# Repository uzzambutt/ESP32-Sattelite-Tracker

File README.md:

<div align="center">

# ESP32 Satellite Tracker — Orbital Ops v10.0

**Designer:** [Muhammad Uzzam Butt](https://github.com/uzzambutt) // Made for Offtrack YSWS

*PCB screenshot, Uses SGP4 to calculate orbital sattelite mechanics natively.*

</div>

An ESP32-based automated satellite tracking system that drives a two-axis antenna mount using stepper motors, propagates satellite positions in real time with the SGP4 algorithm, and serves a live web dashboard over WiFi. The system supports a satellite queue, 24-hour pass scheduling, Doppler shift calculation, IMU-assisted elevation correction, weather data, satellite footprint visualization, and full EasyComm II compatibility for use with applications such as Look4Sat.

---

## Table of Contents

1. [Features](#features)
2. [Hardware Requirements](#hardware-requirements)
3. [Wiring Reference](#wiring-reference)
4. [Software Dependencies](#software-dependencies)
5. [File Structure](#file-structure)
6. [Configuration](#configuration)
7. [secrets.h Setup](#secretsh-setup)
8. [Building and Flashing](#building-and-flashing)
9. [First Boot](#first-boot)
10. [Web Dashboard](#web-dashboard)
11. [TFT Screen Reference](#tft-screen-reference)
12. [REST API Reference](#rest-api-reference)
13. [EasyComm II Interface](#easycomm-ii-interface)
14. [Satellite Queue](#satellite-queue)
15. [Pass Schedule](#pass-schedule)
16. [Weather Integration](#weather-integration)
17. [Auto-Park](#auto-park)
18. [OTA Updates](#ota-updates)
19. [Troubleshooting](#troubleshooting)

---

## Features

**Tracking and Propagation**
- Real-time SGP4/SDP4 satellite position propagation via the Sgp4 Arduino library
- Two-axis antenna control (azimuth and elevation) using AccelStepper with smooth acceleration
- Satellite queue: track up to 8 satellites sequentially, with automatic advancement after each pass
- 24-hour pass schedule computed for all queued satellites simultaneously, sorted by AOS time
- Real-time Doppler frequency shift calculation for multi-band (145.8, 435.8, 1268.0 MHz)
- Accurate satellite footprint computation using true orbital altitude and Earth-radius geometry
- Atmospheric drag refraction correction (Bennett 1982) for low-elevation passes

**Displays**
- 240x320 ST7789 TFT with 6 cycling screens:
  - Main HUD: target/current Az/El, pass countdown, Doppler, range, signal bars, radar
  - Pass Schedule: next 24 h passes for all queued satellites
  - IMU Drift Graph: real-time Kalman error history plot
  - Satellite Footprint: geometrically accurate overhead map with nadir, coverage area, arc angle
  - Orbital Elements: Inclination, RAAN, Eccentricity, Period, Perigee/Apogee, Orbit Type, TLE Age
  - Weather: temperature, feels-like, wind speed/direction, humidity, pressure, NOAA Kp Index
- Animated radar with satellite trajectory, AOS/LOS markers, and physics-based footprint ring
- Linux-style boot log with colour-coded status tags on TFT

**Networking and Control**
- WiFi station mode with AP fallback portal for credential setup
- Web dashboard served from PROGMEM over port 80 (ESPAsyncWebServer)
- WebSocket push telemetry at 1 Hz
- EasyComm II protocol over TCP port 4533 for Look4Sat and compatible clients
- mDNS hostname: sattracker.local
- ArduinoOTA firmware updates over WiFi

**Sensors and Intelligence**
- MPU6050 IMU with two-axis Kalman filter
- Accelerometer spike rejection, gyro deadband, and software low-pass filter
- **Note:** The MPU6050 is a 6-axis IMU (Gyro+Accel) and only measures gravity vectors. It can correct wind-drift or step-skipping on the **Elevation** axis, but it cannot determine absolute Azimuth heading without a magnetometer.
- NTP time synchronisation via pool.ntp.org
- Real-time NOAA Space Weather (Geomagnetic Kp index) parsing

**Persistence**
- TLE stored to LittleFS (/tle.txt) and re-loaded on boot
- Observer grid square, operating mode, weather city, and WiFi credentials stored in NVS (Preferences)

---

## Hardware Requirements

| Component | Notes |
|-----------|-------|
| ESP32 development board | 30-pin or 38-pin, dual-core. Tested on ESP32-WROOM-32 |
| ST7789 TFT display | 240x320, SPI interface, 3.3 V logic |
| MPU6050 / GY-521 | I2C IMU, address 0x68 |
| Azimuth stepper driver | Step/Dir interface (e.g. DRV8825, A4988, TB6600) |
| Elevation stepper driver | Step/Dir interface |
| Azimuth stepper motor | NEMA 17 or NEMA 23 depending on load |
| Elevation stepper motor | NEMA 17 or NEMA 23 depending on load |
| Power supply | 12 V or 24 V for stepper drivers; 3.3 V/5 V for ESP32 |

---

## Wiring Reference

### TFT Display (ST7789, SPI)

| TFT Pin | ESP32 Pin | Config Constant |
|---------|-----------|-----------------|
| CS | GPIO 15 | TFT_CS |
| DC | GPIO 2 | TFT_DC |
| RST | GPIO 4 | TFT_RST |
| SCK | GPIO 18 | Hardware SPI (VSPI) |
| MOSI | GPIO 23 | Hardware SPI (VSPI) |
| VCC | 3.3 V | |
| GND | GND | |

### MPU6050 IMU (I2C)

| MPU6050 Pin | ESP32 Pin | Config Constant |
|-------------|-----------|-----------------|
| VCC | 3.3 V | |
| GND | GND | |
| SDA | GPIO 21 | MPU_SDA |
| SCL | GPIO 22 | MPU_SCL |
| AD0 | GND | Sets I2C address to 0x68 |

### Azimuth Stepper Driver

| Signal | ESP32 Pin | Config Constant |
|--------|-----------|-----------------|
| STEP | GPIO 32 | AZ_STEP |
| DIR | GPIO 14 | AZ_DIR |
| ENABLE | GPIO 25 | ENABLE_PIN (shared with elevation) |

### Elevation Stepper Driver

| Signal | ESP32 Pin | Config Constant |
|--------|-----------|-----------------|
| STEP | GPIO 27 | EL_STEP |
| DIR | GPIO 26 | EL_DIR |
| ENABLE | GPIO 25 | ENABLE_PIN (shared with azimuth) |

### Button

| Function | ESP32 Pin | Notes |
|----------|-----------|-------|
| Screen cycle | GPIO 0 | IO0 / BOOT button. Active LOW, internal pull-up enabled |

---

## Software Dependencies

Install all of the following through the Arduino IDE Library Manager or manually:

| Library | Purpose |
|---------|---------|
| Sgp4 | SGP4/SDP4 orbital propagation |
| Adafruit_GFX | TFT graphics primitives |
| Adafruit_ST7789 | ST7789 TFT driver |
| AccelStepper | Stepper motor control with acceleration profiles |
| ESPAsyncWebServer | Asynchronous HTTP and WebSocket server |
| AsyncTCP | Required by ESPAsyncWebServer |
| ArduinoJson | JSON serialisation and deserialisation |
| NTPClient | NTP time synchronisation |
| ArduinoOTA | Over-the-air firmware updates |
| ESPmDNS | mDNS hostname resolution |
| LittleFS (built-in) | Filesystem for TLE storage |
| Preferences (built-in) | NVS key-value persistent storage |
| HTTPClient (built-in) | OpenWeatherMap API requests |
| Wire (built-in) | I2C communication for MPU6050 |

Board package: Install "ESP32 by Espressif Systems" via Boards Manager.
Tested with Arduino IDE 2.x and ESP32 core 2.0.x or 3.x.

---

## File Structure

```
ESP32_Sat_Tracker/
├── ESP32_Sat_Tracker.ino   Main sketch: globals, setup(), loop(), Core0 task,
│                            web server handlers, SGP4 runner, pass prediction,
│                            queue logic, Doppler, footprint, weather fetch
├── Config.h                 Pin definitions, colour palette, tuning parameters
├── secrets.h                WiFi credentials and OWM API key (excluded from VCS)
├── Display_Module.h         All TFT drawing functions (5 screens + radar engine)
├── Runtime_Module.h         EasyComm II parser and SGP4 runtime update function
├── Web_Pages.h              PROGMEM HTML/CSS/JS dashboard and WiFi setup portal
├── qrcodegen.h              QR code generator (used on boot screen)
└── data/                    LittleFS data directory
```

---

## Configuration

All hardware pins, timing constants, and tuning parameters are defined in Config.h. No other file needs editing for a pin reassignment.

### Key Constants

| Constant | Default | Description |
|----------|---------|-------------|
| BTN_PIN | 0 | GPIO for screen-cycle button |
| SCREEN_COUNT | 5 | Number of TFT screens |
| MAX_QUEUED_SATS | 8 | Maximum satellites in the tracking queue |
| MAX_SCHEDULED_PASSES | 48 | Maximum passes in the 24-hour schedule |
| PARK_IDLE_SEC | 300 | Seconds of inactivity before auto-park |
| PARK_AZ | 0.0 | Park azimuth in degrees |
| PARK_EL | 0.0 | Park elevation in degrees |
| WEATHER_INTERVAL_MS | 600000 | Weather fetch interval in milliseconds (10 min) |
| IMU_CORRECT_ENABLED | false | Enable IMU-assisted elevation correction |
| IMU_CORRECT_THRESH | 2.5 | Error threshold in degrees to trigger IMU correction |

### Steps Per Degree

The stepper resolution is set in the main sketch:

```cpp
const float STEPS_PER_DEG = 8.88f;
```

Calculate your value as:

    STEPS_PER_DEG = (motor_full_steps * driver_microsteps * gear_ratio) / 360

Example: 200 steps/rev * 16 microsteps * 1:1 gearbox / 360 = 8.89 steps/degree.

---

## secrets.h Setup

Create this file in the sketch directory. It is excluded from version control.

```cpp
// secrets.h
#pragma once

static const char* ssid     = "YOUR_WIFI_SSID";
static const char* password = "YOUR_WIFI_PASSWORD";

#define OWM_API_KEY "YOUR_OPENWEATHERMAP_API_KEY"
```

Obtain a free API key at https://openweathermap.org/api. The free tier is sufficient; the tracker uses only the Current Weather Data endpoint.

If OWM_API_KEY is not defined, weather fetching is disabled at compile time.

---

## Building and Flashing

1. Open ESP32_Sat_Tracker.ino in Arduino IDE 2.x.
2. Select your ESP32 board under Tools > Board > ESP32 Arduino.
3. Set the partition scheme to "Minimal SPIFFS (1.9MB APP with OTA)" or "Default 4MB with SPIFFS" under Tools > Partition Scheme.
4. Confirm secrets.h exists in the sketch directory.
5. Click Upload.

The first upload must be over USB. Subsequent uploads can use ArduinoOTA.

---

## First Boot

The TFT shows a Linux-style boot log:

```
[  OK  ]  IMU Kalman p=0.00
[  OK  ]  LittleFS mounted
[  OK  ]  Prefs: grid MM71dl
[ WARN ]  No saved TLE
[  ..  ]  Coupling WiFi radio
[  OK  ]  WiFi link up
[  OK  ]  IP 192.168.x.x
[  OK  ]  mDNS sattracker.local
[  OK  ]  NTP sync OK
[  OK  ]  WX Lahore
[  OK  ]  Starting Ops HUD
```

If WiFi fails after 15 seconds, the tracker creates a hotspot named AEROSPACE-TRACKER with password "groundstation". Browse to 192.168.4.1, enter your WiFi credentials, and the device reboots.

---

## Web Dashboard

Browse to http://sattracker.local or the IP address shown on the TFT.

The dashboard polls /api/status every 500 ms and maintains a live WebSocket connection for push updates. The dashboard is served by the ESP32 over port 80 and provides a complete SpaceX/Tesla style UI with animations and glassmorphism. It includes:

1. **Top Bar**: Weather, NOAA Kp index, UTC clock, status badges, and Night Mode toggle.
2. **Telemetry Stat-Strip**: Real-time Azimuth, Elevation, Range, and Doppler shift.
3. **Tactical Radar**: An animated sweeping radar with ghost trails, target lock beam, footprint ring, and crosshairs. Includes manual joystick controls.
4. **World Map Ground Track**: Real-time display of the satellite over an equirectangular world map with its physics-based visibility footprint.
5. **Orbital Database**: Upload raw 3-line TLEs or pull from Celestrak, view the active queue with live visibility dots, and parse raw orbital elements.
6. **24-Hour Pass Schedule**: Displays upcoming passes with maximum elevations and pass quality grades (A/B/C/F). Can be exported to CSV.
7. **QSO Log**: Store manual QSO/contact logs in your browser's local storage with timestamps.

---

## TFT Screen Reference

Press the IO0 button to cycle through screens.

| Screen | Name | Content |
|--------|------|---------|
| 0 | Main HUD | Target and current Az/El, AOS/LOS/countdown, range, Doppler, status indicators, animated radar with trajectory |
| 1 | Pass Schedule | Next passes for all queued satellites, upcoming passes in green, past in grey |
| 2 | IMU Drift Graph | Real-time plot of IMU pitch error vs. time, with correction threshold markers |
| 3 | Satellite Footprint | Overhead ground map: observer at centre, nadir crosshair, footprint ring centred on nadir point. Shows altitude, slant range, footprint radius, arc angle, coverage area in km2, and percentage of Earth surface covered |
| 4 | Weather | City, condition, temperature with feels-like, wind speed and compass direction, humidity, pressure, wind bar, last fetch time |

---

## REST API Reference

All endpoints are on port 80. Bodies are JSON.

### GET /api/status
Full telemetry payload. Called every 500 ms by the dashboard. Also pushed via WebSocket at /ws at 1 Hz.

### POST /api/tle
Upload a new primary TLE. Inserts at queue position 0 and begins tracking immediately.

    { "name": "ISS (ZARYA)", "line1": "1 25544U ...", "line2": "2 25544 ..." }

### POST /api/queue
Append a satellite to the queue without changing the active satellite.

    { "name": "NOAA 18", "line1": "1 28654U ...", "line2": "2 28654 ..." }

Returns {"status":"ok"} or {"status":"full"}.

### POST /api/queue/remove
Remove a satellite by zero-based index.

    { "idx": 2 }

### POST /api/queue/clear
Remove all satellites from the queue.

### GET /api/schedule
Returns the computed 24-hour pass schedule as a JSON array.

    [ { "sat": "ISS (ZARYA)", "aos": 1750000000, "los": 1750000400, "maxEl": 72.3, "aosAz": 315.1 }, ... ]

### POST /api/schedule/refresh
Triggers an immediate recompute. Call before polling /api/schedule.

### GET /api/path
Predicted trajectory of the current satellite for the radar.

    [ { "az": 315.2, "el": 0.0 }, { "az": 316.8, "el": 4.3 }, ... ]

### GET /api/passlog
Last 10 completed passes.

    [ { "sat": "AO-91", "time": "20:14:30", "maxEl": 34.7 }, ... ]

### POST /api/config
Update observer grid square and/or operating mode.

    { "grid": "MM71dl", "obMode": true }

obMode true = internal SGP4. obMode false = external EasyComm mode.

### POST /api/weather/city
Override weather query location by city name. Persists across reboots. Send an empty string to revert to coordinates.

    { "city": "Lahore" }

### POST /api/manual
Manually command Az/El. Only accepted in external mode.

    { "az": 180.0, "el": 45.0 }

### POST /api/wifi
Submit new WiFi credentials (AP portal only). Triggers reboot.

    { "ssid": "MyNetwork", "pass": "password" }

---

## EasyComm II Interface

The tracker listens on TCP port 4533. Compatible with Look4Sat, GPredict, and Ham Radio Deluxe rotator control.

| Command | Action |
|---------|--------|
| AZ\<value\> EL\<value\> | Set target azimuth and elevation in degrees |
| P \<az\> \<el\> | Positional command (alternate format) |
| P or p | Query current position; responds with AZ\<az\> EL\<el\> |

Movement commands are ignored in internal SGP4 mode.

---

## Satellite Queue

The queue holds up to 8 satellites (MAX_QUEUED_SATS). Position 0 is always the actively tracked satellite.

Adding: Upload via /api/tle to insert at position 0, or /api/queue to append.

Automatic advancement: When a pass ends and the satellite drops below the horizon, the tracker removes it from position 0 and begins tracking the next satellite in the queue.

Persistence: Position 0 is written to LittleFS on every TLE upload and reloaded on boot.

---

## Pass Schedule

The schedule scans the next 24 hours for every queued satellite, finds all visible passes, and stores up to 48 results sorted by AOS time. Computation runs in a dedicated FreeRTOS task on Core 0 to keep the display responsive.

Recompute is triggered automatically on boot, every 30 minutes, when the queue changes, and on demand via POST /api/schedule/refresh.

---

## Weather Integration

Weather data is fetched from OpenWeatherMap every 10 minutes (WEATHER_INTERVAL_MS).

Default mode: coordinates derived from the observer Maidenhead grid square.
City override: POST a city name to /api/weather/city. Stored in NVS. If OpenWeatherMap returns 404 for the city name, the firmware automatically clears the override and reverts to lat/lon.

---

## Auto-Park

In internal SGP4 mode, the antenna moves to PARK_AZ / PARK_EL after PARK_IDLE_SEC seconds of no activity and no active pass window. Any antenna movement resets the idle timer. Auto-park is disabled in external EasyComm mode.

---

## OTA Updates

After the initial USB flash, firmware can be updated wirelessly.

Arduino IDE: the device appears as "sattracker" under Tools > Port > Network Ports.

Command line:

    python espota.py -i sattracker.local -f ESP32_Sat_Tracker.ino.bin

No OTA password is set by default.

---

## Troubleshooting

**Display shows garbage or wrong colours**
Verify TFT_CS, TFT_DC, and TFT_RST in Config.h. Confirm the module is 3.3 V logic and VCC is correctly connected.

**IMU shows OFFLINE**
Check SDA/SCL wiring. The calibration requires the board to be stationary for about 1 second on boot.

**WiFi fails and goes to AP mode every boot**
Credentials are saved to NVS after a successful connection. If the router SSID or password has changed, connect to AEROSPACE-TRACKER and re-enter credentials.

**NTP never syncs**
The tracker uses pool.ntp.org over UDP port 123. Ensure the router does not block UDP port 123 outbound. The TFT HUD shows a red dot until sync succeeds; pass predictions and countdowns require sync.

**Stepper moves in the wrong direction**
Swap the DIR wiring on the affected driver, or swap one motor coil pair.

**Schedule shows passes for only one satellite**
Ensure all satellites are in the queue before clicking REFRESH SCHEDULE. If MAX_SCHEDULED_PASSES (48) is exhausted, increase the constant in Config.h and reflash.

**Weather shows the wrong city**
Send POST /api/weather/city with {"city":""} to clear the override and revert to observer coordinates.

**Screen freezes during schedule computation**
Fixed in v10.0: computeSchedule() now runs in a dedicated FreeRTOS task. If freezes persist, reduce MAX_QUEUED_SATS or MAX_SCHEDULED_PASSES in Config.h.

---

## License

This project is open source. See the repository for license details.

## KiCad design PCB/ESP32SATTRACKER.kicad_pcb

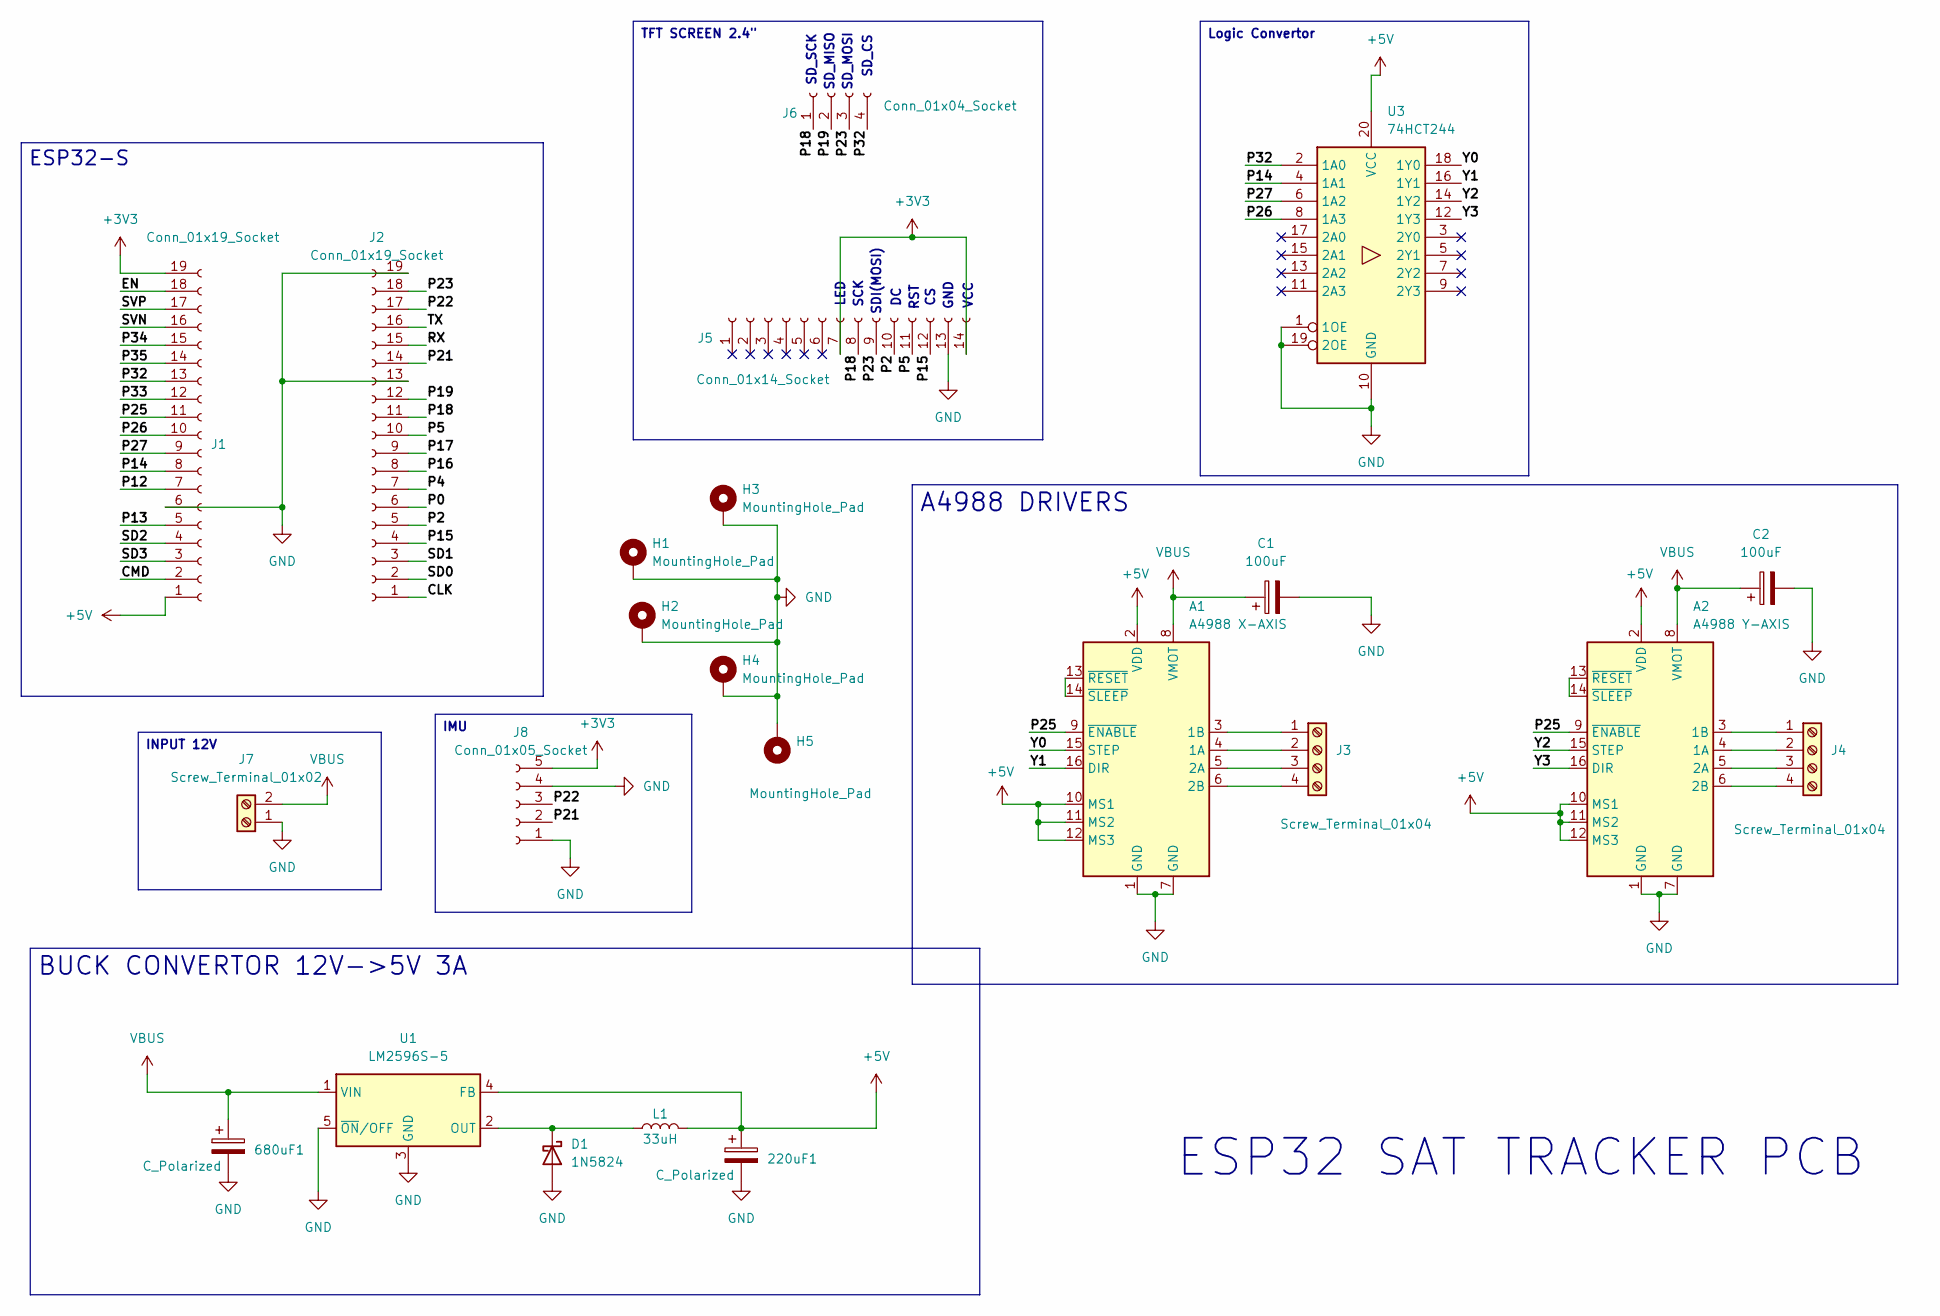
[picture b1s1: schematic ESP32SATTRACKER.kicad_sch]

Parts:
220uF1: C_Polarized; CP_Axial_L11.0mm_D6.0mm_P18.00mm_Horizontal
680uF1: C_Polarized; CP_Axial_L18.0mm_D10.0mm_P25.00mm_Horizontal
A1: A4988 X-AXIS; Pololu_Breakout-16_15.2x20.3mm
A2: A4988 Y-AXIS; Pololu_Breakout-16_15.2x20.3mm
C1, C2: 100uF; CP_Axial_L11.0mm_D6.0mm_P18.00mm_Horizontal
D1: 1N5824; D_DO-201AD_P15.24mm_Horizontal
H1, H2, H3, H4, H5: MountingHole_Pad; MountingHole_2.2mm_M2_Pad
J1, J2: Conn_01x19_Socket; PinSocket_1x19_P2.54mm_Vertical
J3, J4: Screw_Terminal_01x04; TerminalBlock_4Ucon_1x04_P3.50mm_Horizontal
J5: Conn_01x14_Socket; PinHeader_1x14_P2.54mm_Vertical
J6: Conn_01x04_Socket; PinHeader_1x04_P2.54mm_Vertical
J7: Screw_Terminal_01x02; TerminalBlock_4Ucon_1x02_P3.50mm_Vertical
J8: Conn_01x05_Socket; PinHeader_1x05_P2.54mm_Vertical
L1: 33uH; L_12x12mm_H8mm
U1: LM2596S-5; TO-263-5_TabPin3
U3: 74HCT244; DIP-20_W7.62mm

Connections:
+3V3: J1.19, J5.7, J5.14, J8.5
+5V: 220uF1.1, A1.2 (VDD), A1.10 (MS1), A1.11 (MS2), A1.12 (MS3), A2.2 (VDD), A2.10 (MS1), A2.11 (MS2), A2.12 (MS3), J1.1, L1.2, U1.4 (FB), U3.20 (VCC)
/CLK: J2.1
/CMD: J1.2
/EN: J1.18
/P0: J2.6
/P2: J2.5, J5.10
/P4: J2.7
/P5: J2.10, J5.11
/P12: J1.7
/P13: J1.5
/P14: J1.8, U3.4 (1A1)
/P15: J2.4, J5.12
/P16: J2.8
/P17: J2.9
/P18: J2.11, J5.8, J6.1
/P19: J2.12, J6.2
/P21: J2.14, J8.2
/P22: J2.17, J8.3
/P23: J2.18, J5.9, J6.3
/P25: A1.9 (~ENABLE), A2.9 (~ENABLE), J1.11
/P26: J1.10, U3.8 (1A3)
/P27: J1.9, U3.6 (1A2)
/P32: J1.13, J6.4, U3.2 (1A0)
/P33: J1.12
/P34: J1.15
/P35: J1.14
/RX: J2.15
/SD0: J2.2
/SD1: J2.3
/SD2: J1.4
/SD3: J1.3
/SVN: J1.16
/SVP: J1.17
/TX: J2.16
/Y0: A1.15 (STEP), U3.18 (1Y0)
/Y1: A1.16 (DIR), U3.16 (1Y1)
/Y2: A2.15 (STEP), U3.14 (1Y2)
/Y3: A2.16 (DIR), U3.12 (1Y3)
GND: 220uF1.2, 680uF1.2, A1.1 (GND), A1.7 (GND), A2.1 (GND), A2.7 (GND), C1.2, C2.2, D1.2 (A), H1.1, H2.1, H3.1, H4.1, H5.1, J1.6, J2.13, J2.19, J5.13, J7.1, J8.1, J8.4, U1.3 (GND), U1.5 (~ON/OFF), U3.1 (1OE), U3.10 (GND), U3.19 (2OE)
unnamed: A1.4 (1A), J3.2
unnamed: A1.3 (1B), J3.1
unnamed: A1.5 (2A), J3.3
unnamed: A1.6 (2B), J3.4
unnamed: A1.13 (~RESET), A1.14 (~SLEEP)
unnamed: A2.4 (1A), J4.2
unnamed: A2.3 (1B), J4.1
unnamed: A2.5 (2A), J4.3
unnamed: A2.6 (2B), J4.4
unnamed: A2.13 (~RESET), A2.14 (~SLEEP)
unnamed: D1.1 (K), L1.1, U1.2 (OUT)
VBUS: 680uF1.1, A1.8 (VMOT), A2.8 (VMOT), C1.1, C2.1, J7.2, U1.1 (VIN)

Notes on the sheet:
SCK
RST
SDI(MOSI)
SD_MISO
SD_MOSI
SD_CS
ESP32 SAT TRACKER PCB
LED
SD_SCK
VCC
GND
IMU
Logic Convertor
A4988 DRIVERS
TFT SCREEN 2.4"
BUCK CONVERTOR 12V->5V 3A
INPUT 12V
ESP32-S

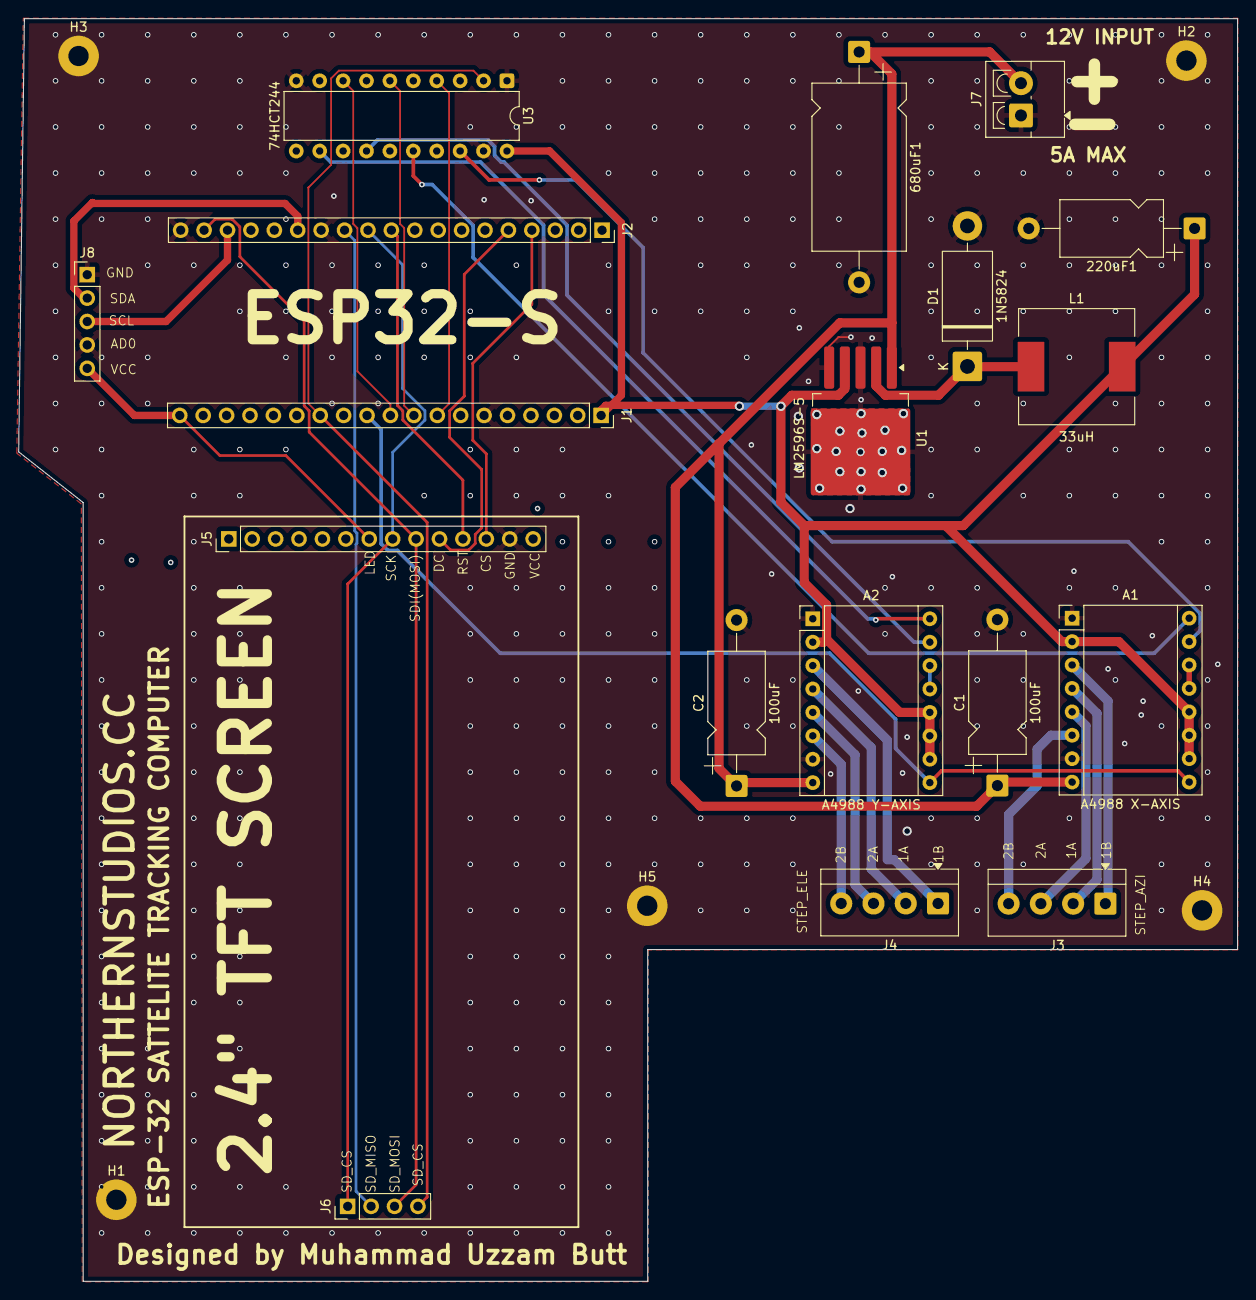
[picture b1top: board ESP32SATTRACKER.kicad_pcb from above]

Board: 2 copper layers, 132.2 x 137.0 mm, 23 parts (0 on the bottom side), 32 nets.

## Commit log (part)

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2026-06-03 ooga booga
2026-06-05 Add ST7789 TFT display support, SGP4 trajectory radar, and watchdog crash fixes
2026-06-05 Update to V6.2: Add QR boot screen, terminal log, and fix watchdog crash
2026-06-06 Update to V6.3: Add QR boot screen, terminal log, and fix watchdog crash
2026-06-06 Update to V8.3 - Fixed older Sat Path not erasing, Shows Azi even when sattelite eclipses.
2026-06-07 Update to V8.3: Added better UI, Animations and added AOS/LOS prediction.
2026-06-10 fixed UI scale
2026-06-11 added vibrant colors
2026-06-12 fix some stuff
2026-06-23 split up files and fixed bugs
2026-06-23 fixed some bugs
2026-06-23 readme.md
2026-06-24 added kp and other TLE info
2026-06-24 Revamp Web Dashboard UI, fix TLE loading & NOAA Space Weather API
2026-06-24 Update README with new UI and IMU notes
2026-06-24 Add Sun/Moon tracking, Polarization Squint, Hardware GPS, and Pre-Winding/Zenith logic

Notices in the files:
README.md:
License: MIT
